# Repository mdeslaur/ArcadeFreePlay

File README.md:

# Patches for arcade games to add Free Play

These directories contain Free Play patches for arcade game roms.

They currently support:
- 1943
- Arkanoid
- Arkanoid: Revenge of Doh
- Atari Starship 1
- Bank Panic
- Bombjack
- Bubble Bobble (Redux)
- Bubble Bobble Lost Cave
- Double Dragon

In addition, there are some enhancement paches for arcade game roms.

They currently support:
- Mario Bros

Change history:  
2024-07-12 - Initial version  
2024-07-13 - Added Bubble Bobble Lost Cave  
2024-07-13 - Added Atari Starship 1  
2025-02-15 - Added Arkanoid: Revenge of Doh  
2025-12-23 - Added High Score saving to Bombjack patches  
2026-10-11 - Added Atari Starship 1 rom adapter pcb  
2026-10-21 - Added Mario Bros enhancement patch  

Marc Deslauriers

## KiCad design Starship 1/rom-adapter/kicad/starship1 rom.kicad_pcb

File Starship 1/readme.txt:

These patches add freeplay to the Atari Starship 1 roms.

Unfortunately, there is no easy way to replace the original Signetics 2600
masked roms with an Eprom as the pinouts are different, an adapter has to
be made to do so. See more info in this thread about Sprint 2:
https://forums.arcade-museum.com/threads/kee-atari-sprint-2-damaged-rom-help.403980/

Once you have made adapters for two of the roms, make sure they work
properly by testing with the original rom images from MAME. After the
adapters have been tested, you can apply the freeplay patches like so:

xdelta3.exe -d -s old\7530-02.h3 7530-02.h3.patch new\7530-02.h3
xdelta3.exe -d -s old\7531-02.e3 7531-02.e3.patch new\7531-02.e3

Freeplay is enabled by setting DIP switches A, B, and C to ON.

Update: RTypeEman from KLOV has provided a kicad file for a PCB to switch
the masked roms to eproms. See the contents of the rom-adapter directory.

Revision History:  
2023-06-14 - Initial version.  
2026-10-11 - Added rom adapter.  

Marc Deslauriers

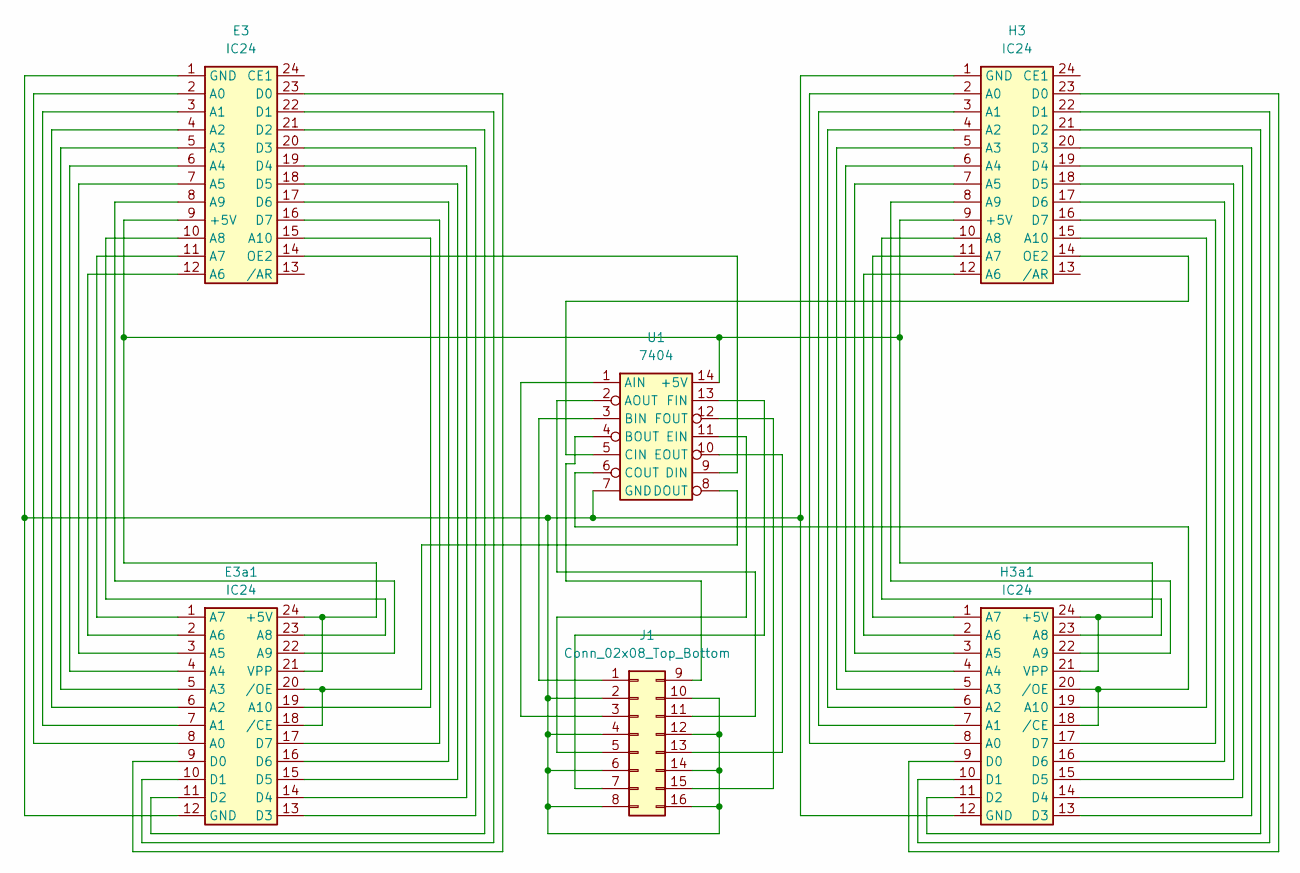
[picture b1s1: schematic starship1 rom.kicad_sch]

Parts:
E3, E3a1: IC24; DIP-24_W15.24mm_Socket_LongPads
H3, H3a1: IC24; DIP-24_W15.24mm_Socket_LongPads
J1: Conn_02x08_Top_Bottom; PinHeader_2x08_P2.54mm_Vertical
U1: 7404; DIP-14_W7.62mm_Socket_LongPads

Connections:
unnamed: E3.2 (A0), E3a1.8 (A0)
unnamed: E3.3 (A1), E3a1.7 (A1)
unnamed: E3.4 (A2), E3a1.6 (A2)
unnamed: E3.5 (A3), E3a1.5 (A3)
unnamed: E3.6 (A4), E3a1.4 (A4)
unnamed: E3.7 (A5), E3a1.3 (A5)
unnamed: E3.8 (A9), E3a1.22 (A9)
unnamed: E3.10 (A8), E3a1.23 (A8)
unnamed: E3.11 (A7), E3a1.1 (A7)
unnamed: E3.12 (A6), E3a1.2 (A6)
unnamed: E3.14 (OE2), U1.9 (DIN)
unnamed: E3.15 (A10), E3a1.19 (A10)
unnamed: E3.16 (D7), E3a1.17 (D7)
unnamed: E3.17 (D6), E3a1.16 (D6)
unnamed: E3.18 (D5), E3a1.15 (D5)
unnamed: E3.19 (D4), E3a1.14 (D4)
unnamed: E3.20 (D3), E3a1.13 (D3)
unnamed: E3.21 (D2), E3a1.11 (D2)
unnamed: E3.22 (D1), E3a1.10 (D1)
unnamed: E3.23 (D0), E3a1.9 (D0)
unnamed: E3a1.18 (/CE), E3a1.20 (/OE), U1.8 (DOUT)
unnamed: E3.1 (GND), E3a1.12 (GND), H3.1 (GND), H3a1.12 (GND), J1.2, J1.4, J1.6, J1.8, J1.10, J1.12, J1.14, J1.16, U1.7 (GND)
unnamed: H3.2 (A0), H3a1.8 (A0)
unnamed: H3.3 (A1), H3a1.7 (A1)
unnamed: H3.4 (A2), H3a1.6 (A2)
unnamed: H3.5 (A3), H3a1.5 (A3)
unnamed: H3.6 (A4), H3a1.4 (A4)
unnamed: H3.7 (A5), H3a1.3 (A5)
unnamed: H3.8 (A9), H3a1.22 (A9)
unnamed: E3.9 (+5V), E3a1.21 (VPP), E3a1.24 (+5V), H3.9 (+5V), H3a1.21 (VPP), H3a1.24 (+5V), U1.14 (+5V)
unnamed: H3.10 (A8), H3a1.23 (A8)
unnamed: H3.11 (A7), H3a1.1 (A7)
unnamed: H3.12 (A6), H3a1.2 (A6)
unnamed: H3.14 (OE2), U1.5 (CIN)
unnamed: H3.15 (A10), H3a1.19 (A10)
unnamed: H3.16 (D7), H3a1.17 (D7)
unnamed: H3.17 (D6), H3a1.16 (D6)
unnamed: H3.18 (D5), H3a1.15 (D5)
unnamed: H3.19 (D4), H3a1.14 (D4)
unnamed: H3.20 (D3), H3a1.13 (D3)
unnamed: H3.21 (D2), H3a1.11 (D2)
unnamed: H3.22 (D1), H3a1.10 (D1)
unnamed: H3.23 (D0), H3a1.9 (D0)
unnamed: H3a1.18 (/CE), H3a1.20 (/OE), U1.6 (COUT)
unnamed: J1.1, U1.3 (BIN)
unnamed: J1.3, U1.1 (AIN)
unnamed: J1.5, U1.11 (EIN)
unnamed: J1.7, U1.13 (FIN)
unnamed: J1.11, U1.2 (AOUT)
unnamed: J1.9, U1.4 (BOUT)
unnamed: J1.13, U1.10 (EOUT)
unnamed: J1.15, U1.12 (FOUT)

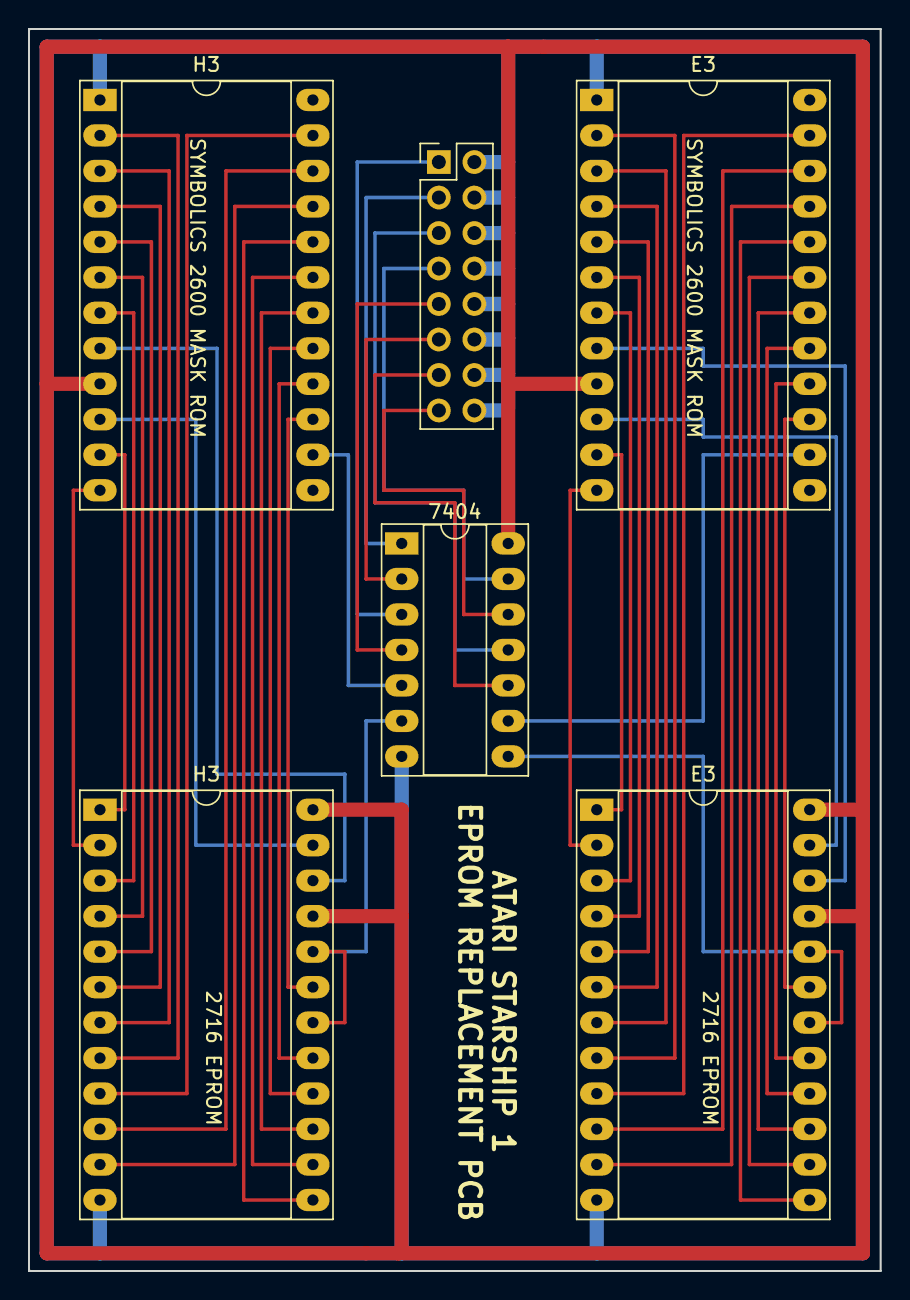
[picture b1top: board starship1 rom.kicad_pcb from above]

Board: 2 copper layers, 61.0 x 88.9 mm, 6 parts (0 on the bottom side), 52 nets.

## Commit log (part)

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2024-07-12 added toplevel README.md file
2024-07-13 renamed Bubble Bobble directory to Bubble Bobble Redux
2024-07-13 Added Bubble Bobble Lost Cave
2024-07-13 added Atari Starship 1
2025-02-15 Added Arkanoid: Revenge of Doh
2025-02-15 fix whitespace in README.md
2025-02-15 fix typo
2025-02-15 added hss patches for japan and bootleg romsets
2025-02-15 added warning to arkanoid 2 readme.txt
2025-03-06 added comment about dip switches to Startship 1 readme.txt
2025-12-23 Added high score saving patch to Bombjack patches
2025-12-23 Added mame patch to help Bombjack testing
2025-12-23 Added MAME patch to help with Starship 1 testing
2025-12-24 Added note about Arcade Rom Patcher
